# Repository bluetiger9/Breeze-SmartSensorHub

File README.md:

# Breeze: Smart Environmental Sensor Hub

Battery & Solar powered Sensor Hub with ML capabilities and supports a wide variety of Sensors and Communication Modules.

**Hackster.io**:
https://www.hackster.io/bluetiger9/breeze-smart-environmental-sensor-hub-fa496e

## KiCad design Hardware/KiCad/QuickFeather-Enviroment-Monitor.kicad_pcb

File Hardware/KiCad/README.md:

# QuickFeather-Enviroment-Monitor

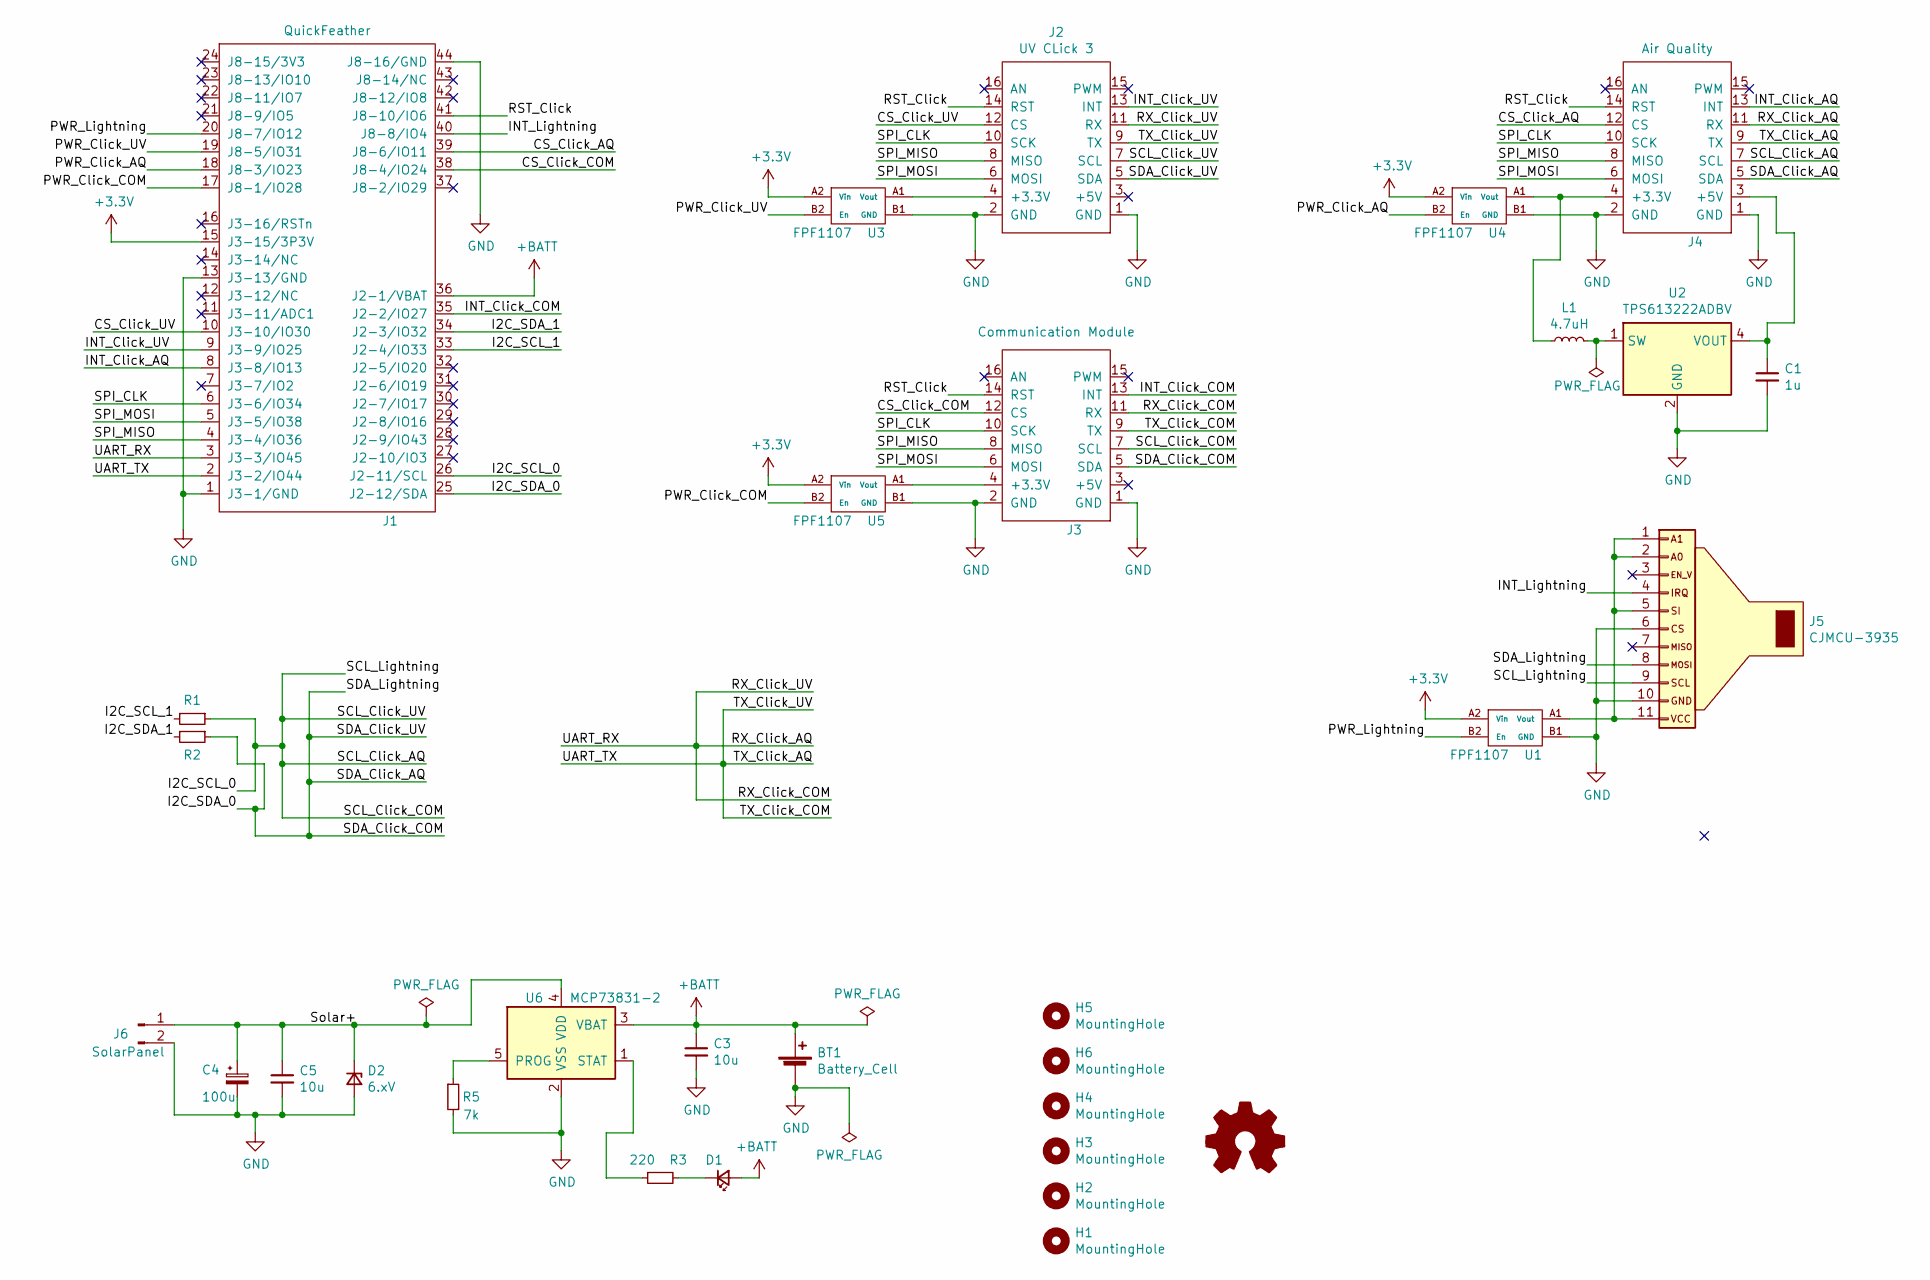
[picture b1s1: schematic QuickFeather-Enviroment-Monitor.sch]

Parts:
BT1: Battery_Cell; BatteryHolder_Keystone_1042_1x18650
C1: 1u; C_0805_2012Metric
C3, C5: 10u; C_0805_2012Metric
C4: 100u; CP_Radial_D6.3mm_P2.50mm
D1: LED_Small; LED_0805_2012Metric
D2: 6.xV; D_SMA
H1, H2, H3, H4, H5, H6: MountingHole
J1: QuickFeather; quickfeather
J2: UV CLick 3; MikroBUS-Small
J3: Communication Module; MikroBUS-Medium
J4: Air Quality; MikroBUS-Small
J5: CJMCU-3935
J6: SolarPanel; PinHeader_1x02_P2.54mm_Vertical
L1: 4.7uH; L_0805_2012Metric
R1, R2: nc; R_0402_1005Metric_Pad0.72x0.64mm_HandSolder
R3: 220; R_0805_2012Metric
R5: 7k; R_0805_2012Metric
U1, U3, U4, U5: FPF1107; BGA4C40P2X2_84X84X60N
U2: TPS613222ADBV; SOT-23-5
U6: MCP73831-2; SOT-23-5

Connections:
+3V3: J1.15 (J3-15/3P3V), U1.A2 (Vin), U3.A2 (Vin), U4.A2 (Vin), U5.A2 (Vin)
+BATT: BT1.1 (+), C3.1, D1.2 (A), J1.36 (J2-1/VBAT), U6.3 (VBAT)
/CS_Click_AQ: J1.39 (J8-6/IO11), J4.12 (CS)
/CS_Click_COM: J1.38 (J8-4/IO24), J3.12 (CS)
/CS_Click_UV: J1.10 (J3-10/IO30), J2.12 (CS)
/I2C_SCL_0: J1.26 (J2-11/SCL), J2.7 (SCL), J3.7 (SCL), J4.7 (SCL), J5.9, R1.1
/I2C_SCL_1: J1.33 (J2-4/IO33), R1.2
/I2C_SDA_0: J1.25 (J2-12/SDA), J2.5 (SDA), J3.5 (SDA), J4.5 (SDA), J5.8, R2.1
/I2C_SDA_1: J1.34 (J2-3/IO32), R2.2
/INT_Click_AQ: J1.8 (J3-8/IO13), J4.13 (INT)
/INT_Click_COM: J1.35 (J2-2/IO27), J3.13 (INT)
/INT_Click_UV: J1.9 (J3-9/IO25), J2.13 (INT)
/INT_Lightning: J1.40 (J8-8/IO4), J5.4
/PWR_Click_AQ: J1.18 (J8-3/IO23), U4.B2 (En)
/PWR_Click_COM: J1.17 (J8-1/IO28), U5.B2 (En)
/PWR_Click_UV: J1.19 (J8-5/IO31), U3.B2 (En)
/PWR_Lightning: J1.20 (J8-7/IO12), U1.B2 (En)
/RST_Click: J1.41 (J8-10/IO6), J2.14 (RST), J3.14 (RST), J4.14 (RST)
/RX_Click_AQ: J1.3 (J3-3/IO45), J2.11 (RX), J3.11 (RX), J4.11 (RX)
/SPI_CLK: J1.6 (J3-6/IO34), J2.10 (SCK), J3.10 (SCK), J4.10 (SCK)
/SPI_MISO: J1.4 (J3-4/IO36), J2.8 (MISO), J3.8 (MISO), J4.8 (MISO)
/SPI_MOSI: J1.5 (J3-5/IO38), J2.6 (MOSI), J3.6 (MOSI), J4.6 (MOSI)
/Solar+: C4.1, C5.1, D2.1 (K), J6.1, U6.4 (VDD)
/TX_Click_AQ: J1.2 (J3-2/IO44), J2.9 (TX), J3.9 (TX), J4.9 (TX)
GND: BT1.2 (-), C1.2, C3.2, C4.2, C5.2, D2.2 (A), J1.1 (J3-1/GND), J1.13 (J3-13/GND), J1.44 (J8-16/GND), J2.1 (GND), J2.2 (GND), J3.1 (GND), J3.2 (GND), J4.1 (GND), J4.2 (GND), J5.6, J5.10, J6.2, R5.2, U1.B1 (GND), U2.2 (GND), U3.B1 (GND), U4.B1 (GND), U5.B1 (GND), U6.2 (VSS)
unnamed: C1.1, J4.3 (+5V), U2.4 (VOUT)
unnamed: D1.1 (K), R3.2
unnamed: J2.4 (+3.3V), U3.A1 (Vout)
unnamed: J3.4 (+3.3V), U5.A1 (Vout)
unnamed: J4.4 (+3.3V), L1.1, U4.A1 (Vout)
unnamed: J5.1, J5.2, J5.5, J5.11, U1.A1 (Vout)
unnamed: L1.2, U2.1 (SW)
unnamed: R3.1, U6.1 (STAT)
unnamed: R5.1, U6.5 (PROG)

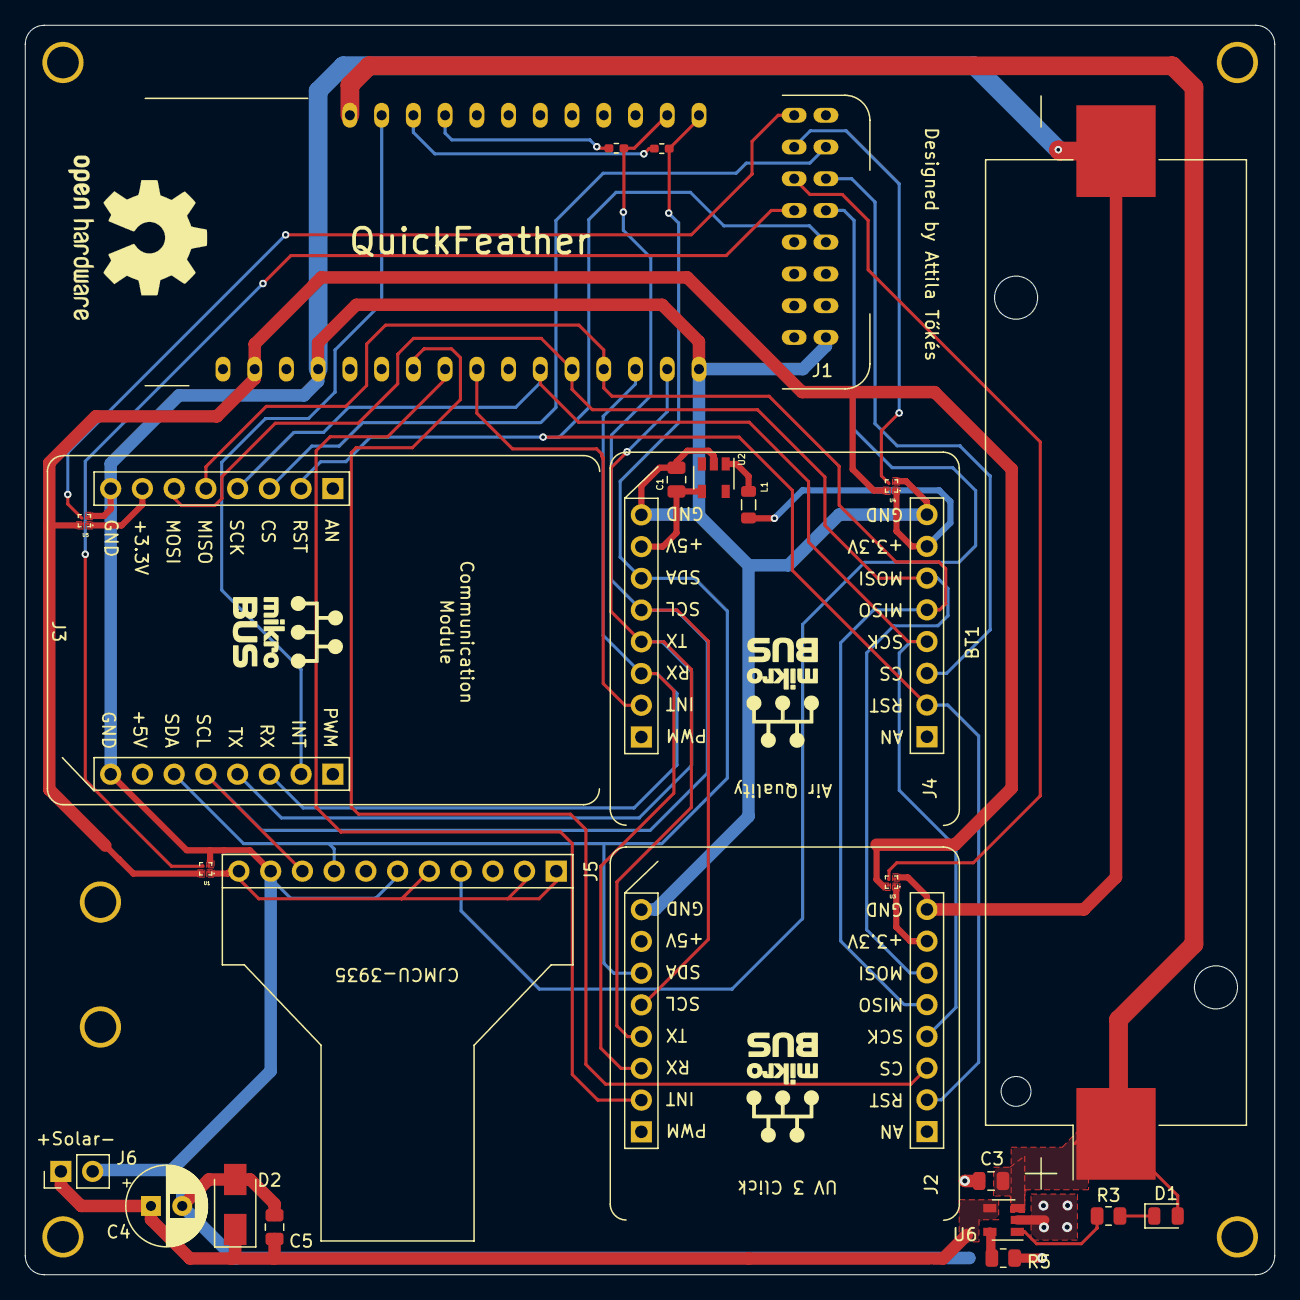
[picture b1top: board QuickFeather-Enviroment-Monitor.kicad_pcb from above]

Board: 2 copper layers, 100.0 x 100.0 mm, 30 parts (0 on the bottom side), 34 nets.

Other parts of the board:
H5#2: MountingHole; MPAD

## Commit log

2021-03-31 KiCad project
2021-03-31 Firmware - initial version
2021-04-04 UV 3 Click / VEML6070 driver
2021-04-04 CJMCU-3935 / AS3935 Lightning sensor driver
2021-04-11 GPIO driver (normal + FPGA) for Power and Chip Select pins
2021-04-11 FPGA design for GPIO control
2021-04-13 PMS7003 driver
2021-04-14 Wifi ESP Click / Communication Module driver + protocol
2021-04-15 Gateway Application (initial commit)
    Source: https://github.com/sensiml/simple-streaming-gateway.git
2021-04-15 Gateway: add TCP Server mode
2021-04-15 Gateway: fix Column ordering
2021-04-18 Firmware: add Earthquake detection knowledge pack
2021-04-18 Firmware: calibrate accelerometer
2021-04-21 Add Earthquake SensiML Model
2021-05-29 InfluxDB + Grafana recording + other stuff
2021-05-29 Firmware - latest changes
2024-01-03 Bump plotly.js from 1.58.4 to 2.25.2 in /Gateway/webui
    Bumps [plotly.js](https://github.com/plotly/plotly.js) from 1.58.4 to 2.25.2.
    - [Release notes](https://github.com/plotly/plotly.js/releases)
    - [Changelog](https://github.com/plotly/plotly.js/blob/master/CHANGELOG.md)
    - [Commits](https://github.com/plotly/plotly.js/compare/v1.58.4...v2.25.2)
    ---
    updated-dependencies:
2024-01-03 Bump minimist from 1.2.5 to 1.2.8 in /Gateway/webui
    Bumps [minimist](https://github.com/minimistjs/minimist) from 1.2.5 to 1.2.8.
    - [Changelog](https://github.com/minimistjs/minimist/blob/main/CHANGELOG.md)
    - [Commits](https://github.com/minimistjs/minimist/compare/v1.2.5...v1.2.8)
    ---
    updated-dependencies:
    - dependency-name: minimist
2024-01-03 Bump @babel/traverse from 7.12.12 to 7.23.7 in /Gateway/webui
    Bumps [@babel/traverse](https://github.com/babel/babel/tree/HEAD/packages/babel-traverse) from 7.12.12 to 7.23.7.
    - [Release notes](https://github.com/babel/babel/releases)
    - [Changelog](https://github.com/babel/babel/blob/main/CHANGELOG.md)
    - [Commits](https://github.com/babel/babel/commits/v7.23.7/packages/babel-traverse)
    ---
    updated-dependencies:
2024-01-03 Bump eventsource from 1.0.7 to 1.1.2 in /Gateway/webui
    Bumps [eventsource](https://github.com/EventSource/eventsource) from 1.0.7 to 1.1.2.
    - [Changelog](https://github.com/EventSource/eventsource/blob/master/HISTORY.md)
    - [Commits](https://github.com/EventSource/eventsource/compare/v1.0.7...v1.1.2)
    ---
    updated-dependencies:
    - dependency-name: eventsource
2024-01-03 Bump url-parse from 1.4.7 to 1.5.10 in /Gateway/webui
    Bumps [url-parse](https://github.com/unshiftio/url-parse) from 1.4.7 to 1.5.10.
    - [Commits](https://github.com/unshiftio/url-parse/compare/1.4.7...1.5.10)
    ---
    updated-dependencies:
    - dependency-name: url-parse
    dependency-type: indirect
